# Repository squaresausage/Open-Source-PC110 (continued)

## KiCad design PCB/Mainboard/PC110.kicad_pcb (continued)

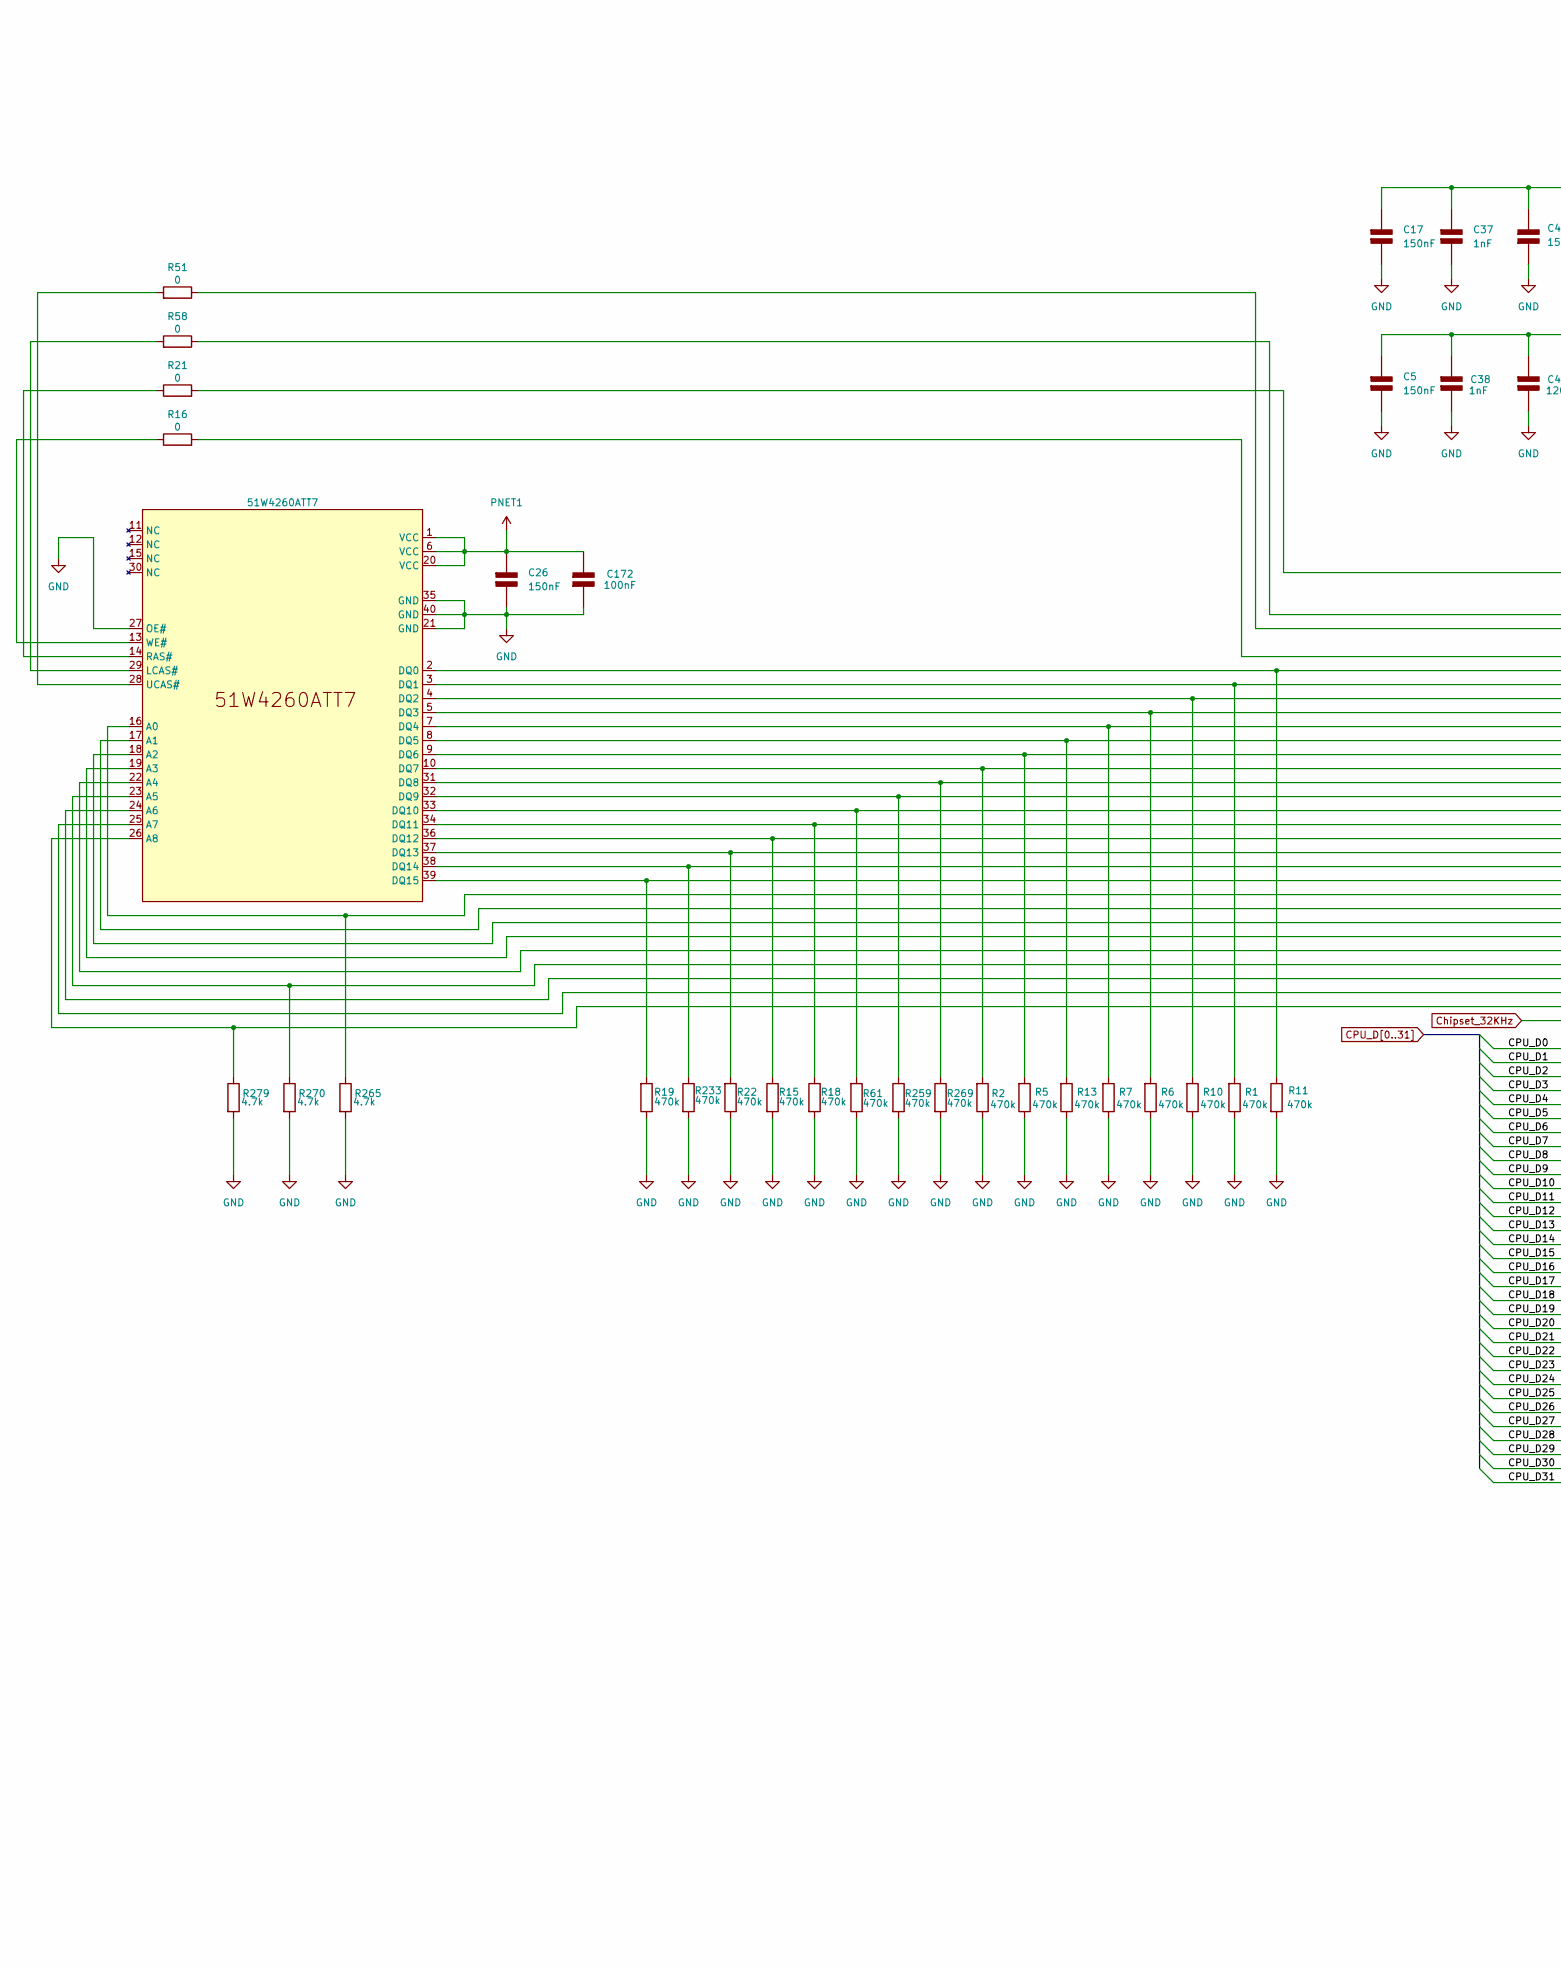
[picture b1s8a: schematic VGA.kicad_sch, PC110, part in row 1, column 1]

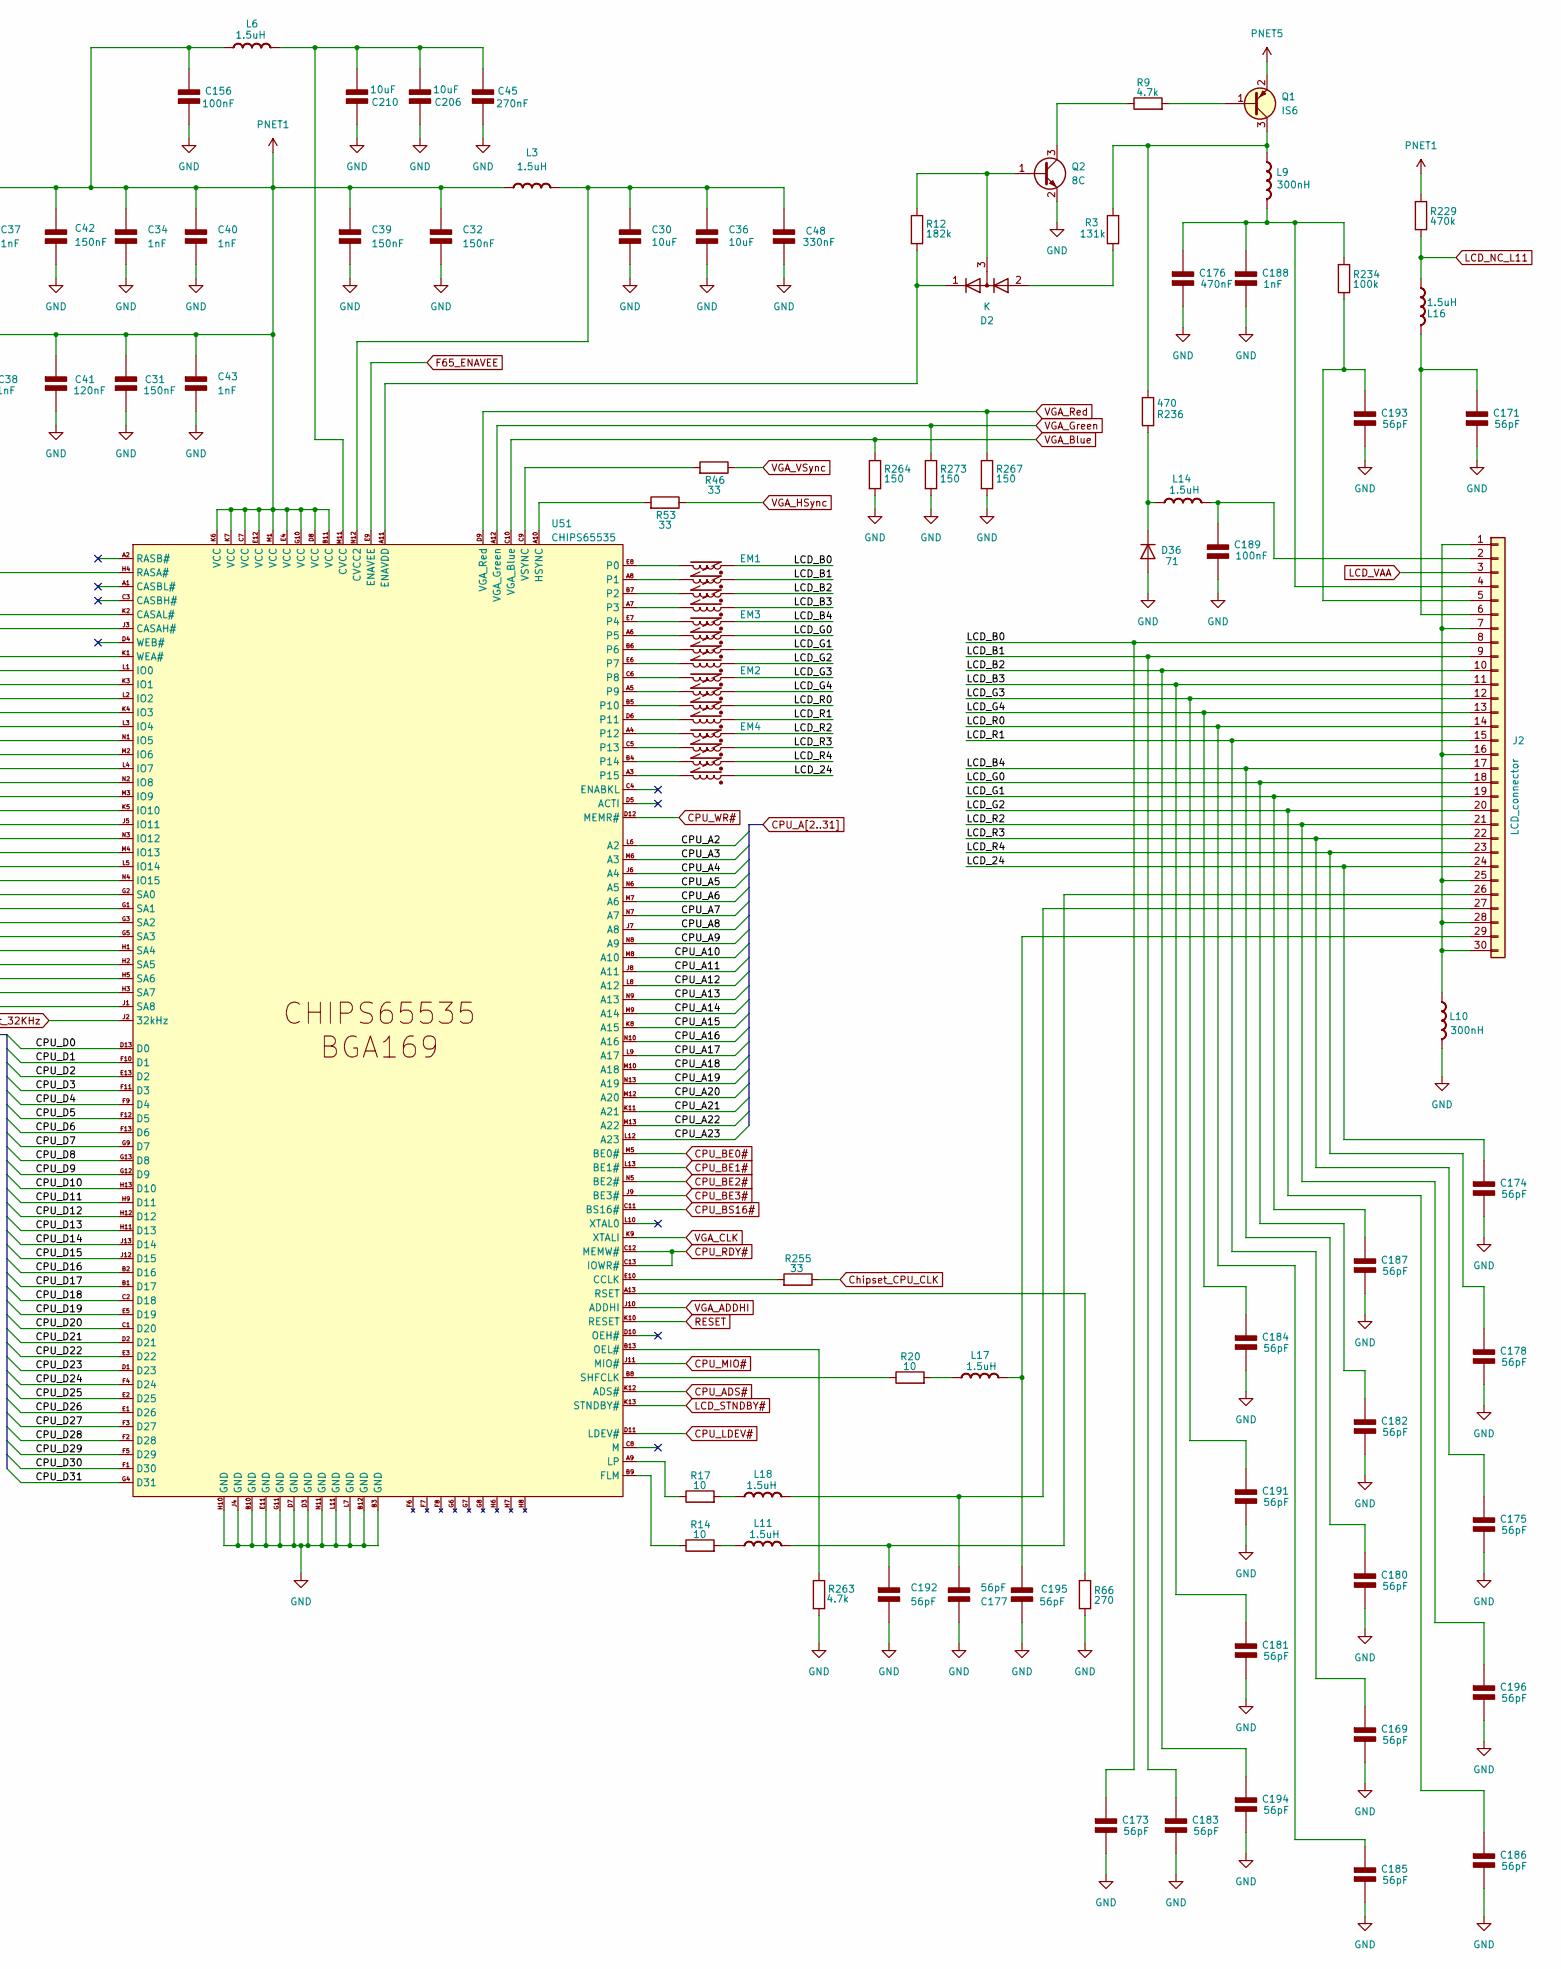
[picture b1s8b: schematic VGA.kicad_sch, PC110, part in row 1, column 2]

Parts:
C5, C17, C26, C31, C32, C39, C42: 150nF; C_0402_1005Metric
C30, C36, C206, C210: 10uF; C_1206_3216Metric
C34, C37, C38, C40, C43, C188: 1nF; C_0402_1005Metric
C41: 120nF; C_0402_1005Metric
C45: 270nF; C_0603_1608Metric
C48: 330nF; C_0402_1005Metric
C156, C172, C189: 100nF; C_0402_1005Metric
C169, C171, C173, C174, C175, C177, C178, C180, C181, C182, C183, C184, C185, C186, C187, C191, C192, C193, C194, C195, C196: 56pF; C_0402_1005Metric
C176: 470nF; C_0603_1608Metric
D2: K; SOT-416L
D36: 71; D_0603_1608Metric
EM1, EM2, EM3, EM4: R-array
J2: LCD_connector
L3, L6, L11, L14, L16, L17, L18: 1.5uH; L_0603_1608Metric
L9, L10: 300nH; L_0805_2012Metric
Q1: IS6; SOT-23
Q2: 8C; SOT-416
R1, R2, R5, R6, R7, R10, R11, R13, R15, R18, R19, R22, R61, R229, R233, R259, R269: 470k; R_0402_1005Metric
R3: 131k; R_0402_1005Metric
R9, R263, R265, R270, R279: 4.7k; R_0402_1005Metric
R12: 182k; R_0402_1005Metric
R14, R17, R20: 10; R_0402_1005Metric
R16, R21, R51, R58: 0; R_0402_1005Metric
R46, R53, R255: 33; R_0402_1005Metric
R66: 270; R_0402_1005Metric
R234: 100k; R_0402_1005Metric
R236: 470; R_0402_1005Metric
R264, R267, R273: 150; R_0805_2012Metric
U8: 51W4260ATT7; GRAMchip
U51: CHIPS65535; BGA-169

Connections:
/VGA Controller/LCD_24: C174.1 (+), EM4.1, J2.24
/VGA Controller/LCD_B0: C173.1 (+), EM1.4, J2.8
/VGA Controller/LCD_B1: C183.1 (+), EM1.3, J2.9
/VGA Controller/LCD_B2: C194.1 (+), EM1.2, J2.10
/VGA Controller/LCD_B3: C181.1 (+), EM1.1, J2.11
/VGA Controller/LCD_B4: C180.1 (+), EM3.4, J2.17
/VGA Controller/LCD_G0: C182.1 (+), EM3.3, J2.18
/VGA Controller/LCD_G1: C187.1 (+), EM3.2, J2.19
/VGA Controller/LCD_G2: C186.1 (+), EM3.1, J2.20
/VGA Controller/LCD_G3: C191.1 (+), EM2.4, J2.12
/VGA Controller/LCD_G4: C184.1 (+), EM2.3, J2.13
/VGA Controller/LCD_R0: C185.1 (+), EM2.2, J2.14
/VGA Controller/LCD_R1: C169.1 (+), EM2.1, J2.15
/VGA Controller/LCD_R2: C196.1 (+), EM4.4, J2.21
/VGA Controller/LCD_R3: C175.1 (+), EM4.3, J2.22
/VGA Controller/LCD_R4: C178.1 (+), EM4.2, J2.23
CPU_A2: U51.L6 (A2); also elsewhere on the board
CPU_A3: U51.M6 (A3); also elsewhere on the board
CPU_A4: U51.J6 (A4); also elsewhere on the board
CPU_A5: U51.N6 (A5); also elsewhere on the board
CPU_A6: U51.M7 (A6); also elsewhere on the board
CPU_A7: U51.N7 (A7); also elsewhere on the board
CPU_A8: U51.J7 (A8); also elsewhere on the board
CPU_A9: U51.N8 (A9); also elsewhere on the board
CPU_A10: U51.M8 (A10); also elsewhere on the board
CPU_A11: U51.J8 (A11); also elsewhere on the board
CPU_A12: U51.L8 (A12); also elsewhere on the board
CPU_A13: U51.N9 (A13); also elsewhere on the board
CPU_A14: U51.M9 (A14); also elsewhere on the board
CPU_A15: U51.K8 (A15); also elsewhere on the board
CPU_A16: U51.N10 (A16); also elsewhere on the board
CPU_A17: U51.L9 (A17); also elsewhere on the board
CPU_A18: U51.M10 (A18); also elsewhere on the board
CPU_A19: U51.N13 (A19); also elsewhere on the board
CPU_A20: U51.M12 (A20); also elsewhere on the board
CPU_A21: U51.K11 (A21); also elsewhere on the board
CPU_A22: U51.M13 (A22); also elsewhere on the board
CPU_A23: U51.L12 (A23); also elsewhere on the board
CPU_ADS#: U51.K12 (ADS#); also elsewhere on the board
CPU_BE0#: U51.M5 (BE0#); also elsewhere on the board
CPU_BE1#: U51.L13 (BE1#); also elsewhere on the board
CPU_BE2#: U51.N5 (BE2#); also elsewhere on the board
CPU_BE3#: U51.J9 (BE3#); also elsewhere on the board
CPU_BS16#: U51.C11 (BS16#); also elsewhere on the board
CPU_D0: U51.D13 (D0); also elsewhere on the board
CPU_D1: U51.F10 (D1); also elsewhere on the board
CPU_D2: U51.E13 (D2); also elsewhere on the board
CPU_D3: U51.F11 (D3); also elsewhere on the board
CPU_D4: U51.F9 (D4); also elsewhere on the board
CPU_D5: U51.F12 (D5); also elsewhere on the board
CPU_D6: U51.F13 (D6); also elsewhere on the board
CPU_D7: U51.G9 (D7); also elsewhere on the board
CPU_D8: U51.G13 (D8); also elsewhere on the board
CPU_D9: U51.G12 (D9); also elsewhere on the board
CPU_D10: U51.H13 (D10); also elsewhere on the board
CPU_D11: U51.H9 (D11); also elsewhere on the board
CPU_D12: U51.H12 (D12); also elsewhere on the board
CPU_D13: U51.H11 (D13); also elsewhere on the board
CPU_D14: U51.J13 (D14); also elsewhere on the board
CPU_D15: U51.J12 (D15); also elsewhere on the board
CPU_D16: U51.B2 (D16); also elsewhere on the board
CPU_D17: U51.B1 (D17); also elsewhere on the board
CPU_D18: U51.C2 (D18); also elsewhere on the board
CPU_D19: U51.E5 (D19); also elsewhere on the board
CPU_D20: U51.C1 (D20); also elsewhere on the board
CPU_D21: U51.D2 (D21); also elsewhere on the board
CPU_D22: U51.E3 (D22); also elsewhere on the board
CPU_D23: U51.D1 (D23); also elsewhere on the board
CPU_D24: U51.F4 (D24); also elsewhere on the board
CPU_D25: U51.E2 (D25); also elsewhere on the board
CPU_D26: U51.E1 (D26); also elsewhere on the board
CPU_D27: U51.F3 (D27); also elsewhere on the board
CPU_D28: U51.F2 (D28); also elsewhere on the board
CPU_D29: U51.F5 (D29); also elsewhere on the board
CPU_D30: U51.F1 (D30); also elsewhere on the board
CPU_D31: U51.G4 (D31); also elsewhere on the board
CPU_LDEV#: U51.D11 (LDEV#); also elsewhere on the board
CPU_MIO#: U51.J11 (MIO#); also elsewhere on the board
CPU_RDY#: U51.C12 (MEMW#), U51.C13 (IOWR#); also elsewhere on the board
CPU_WR#: U51.D12 (MEMR#); also elsewhere on the board
Chipset_32KHz: U51.J2 (32kHz); also elsewhere on the board
Chipset_CPU_CLK: R255.1; also elsewhere on the board
F65_ENAVEE: U51.E9 (ENAVEE); also elsewhere on the board
LCD_NC_L11: L16.2 (-), R229.1; also elsewhere on the board
LCD_STNDBY#: U51.K13 (STNDBY#); also elsewhere on the board
LCD_VAA: J2.3; also elsewhere on the board
unnamed: C30.2 (-), C36.2 (-), C48.1 (+), L3.2 (-), U51.N12 (CVCC2)
unnamed: C171.1 (+), J2.6, L16.1 (+)
unnamed: C176.1 (+), C188.1 (+), J2.4, L9.1 (+), R234.2
unnamed: C177.2 (-), J2.27, L18.1 (+)
unnamed: C189.2 (-), J2.2, L14.1 (+)
unnamed: C192.1 (+), J2.26, L11.2 (-)
unnamed: C193.1 (+), J2.5, R234.1
unnamed: C195.2 (-), J2.29, L17.2 (-)
unnamed: C45.1 (+), C206.2 (-), C210.2 (-), L6.1 (+), U51.M11 (CVCC)
unnamed: D2.2 (A), R3.1
unnamed: D2.1 (K), R12.2, U51.A11 (ENAVDD)
unnamed: D2.3 (common), Q2.1 (B), R12.1
unnamed: D36.1 (K), L14.2 (-), R236.2
unnamed: J2.1, J2.7, J2.16, J2.25, J2.28, J2.30, L10.1 (+)
unnamed: L9.2 (-), Q1.3 (C), R3.2, R236.1
unnamed: L11.1 (+), R14.2
unnamed: L17.1 (+), R20.2
unnamed: L18.2 (-), R17.2
unnamed: Q1.1 (B), R9.2
unnamed: Q2.3 (C), R9.1
unnamed: R58.2, U8.29 (LCAS#)
unnamed: R21.1, U8.14 (RAS#)
unnamed: R51.2, U8.28 (UCAS#)
unnamed: R16.1, U8.13 (WE#)
unnamed: R51.1, U51.J3 (CASAH#)
unnamed: R58.1, U51.K2 (CASAL#)
unnamed: R255.2, U51.E10 (CCLK)
unnamed: R14.1, U51.B9 (FLM)
unnamed: R53.2, U51.A10 (HSYNC)
unnamed: R11.1, U8.2 (DQ0), U51.L1 (IO0)
unnamed: R1.2, U8.3 (DQ1), U51.K3 (IO1)
unnamed: R10.2, U8.4 (DQ2), U51.L2 (IO2)
unnamed: R6.2, U8.5 (DQ3), U51.K4 (IO3)
unnamed: R7.2, U8.7 (DQ4), U51.L3 (IO4)
unnamed: R13.2, U8.8 (DQ5), U51.N1 (IO5)
unnamed: R5.2, U8.9 (DQ6), U51.M2 (IO6)
unnamed: R2.2, U8.10 (DQ7), U51.L4 (IO7)
unnamed: R269.1, U8.31 (DQ8), U51.N2 (IO8)
unnamed: R259.1, U8.32 (DQ9), U51.M3 (IO9)
unnamed: R61.2, U8.33 (DQ10), U51.K5 (IO10)
unnamed: R18.1, U8.34 (DQ11), U51.J5 (IO11)
unnamed: R15.1, U8.36 (DQ12), U51.N3 (IO12)
unnamed: R22.2, U8.37 (DQ13), U51.M4 (IO13)
unnamed: R233.1, U8.38 (DQ14), U51.L5 (IO14)
unnamed: R19.2, U8.39 (DQ15), U51.N4 (IO15)
unnamed: R17.1, U51.A9 (LP)
unnamed: R263.1, U51.B13 (OEL#)
unnamed: EM1.5, U51.E8 (P0)
unnamed: EM1.6, U51.A8 (P1)
unnamed: EM1.7, U51.B7 (P2)
unnamed: EM1.8, U51.A7 (P3)
unnamed: EM3.5, U51.E7 (P4)
unnamed: EM3.6, U51.A6 (P5)
unnamed: EM3.7, U51.B6 (P6)
unnamed: EM3.8, U51.E6 (P7)
unnamed: EM2.5, U51.C6 (P8)
unnamed: EM2.6, U51.A5 (P9)
unnamed: EM2.7, U51.B5 (P10)
unnamed: EM2.8, U51.D6 (P11)
unnamed: EM4.5, U51.A4 (P12)
unnamed: EM4.6, U51.C5 (P13)
unnamed: EM4.7, U51.B4 (P14)
unnamed: EM4.8, U51.A3 (P15)
unnamed: R21.2, U51.H4 (RASA#)
unnamed: R66.2, U51.A13 (RSET)
unnamed: R265.1, U8.16 (A0), U51.G2 (SA0)
unnamed: U8.17 (A1), U51.G1 (SA1)
unnamed: U8.18 (A2), U51.G3 (SA2)
unnamed: U8.19 (A3), U51.G5 (SA3)
unnamed: U8.22 (A4), U51.H1 (SA4)
unnamed: R270.1, U8.23 (A5), U51.H2 (SA5)
unnamed: U8.24 (A6), U51.H5 (SA6)
unnamed: U8.25 (A7), U51.H3 (SA7)
unnamed: R279.1, U8.26 (A8), U51.J1 (SA8)
unnamed: R20.1, U51.B8 (SHFCLK)
unnamed: R46.2, U51.C9 (VSYNC)
unnamed: R16.2, U51.K1 (WEA#)
PNET1: C5.1 (+), C17.1 (+), C26.1 (+), C31.2 (-), C32.1 (+), C34.1 (+), C37.1 (+), C38.1 (+), C39.1 (+), C40.1 (+), C41.1 (+), C42.2 (-), C43.1 (+), C156.2 (-), C172.2 (-), L3.1 (+), L6.2 (-), R229.2, U8.1 (VCC), U8.6 (VCC), U8.20 (VCC), U51.B11 (VCC), U51.C7 (VCC), U51.D8 (VCC), U51.E4 (VCC), U51.E12 (VCC), U51.G10 (VCC), U51.K6 (VCC), U51.K7 (VCC), U51.M1 (VCC); also elsewhere on the board
RESET: U51.K10 (RESET); also elsewhere on the board
VGA_ADDHI: U51.J10 (ADDHI); also elsewhere on the board
VGA_Blue: R264.1, U51.C10 (VGA_Blue); also elsewhere on the board
VGA_CLK: U51.K9 (XTALI); also elsewhere on the board
VGA_Green: R273.1, U51.A12 (VGA_Green); also elsewhere on the board
VGA_HSync: R53.1; also elsewhere on the board
VGA_Red: R267.1, U51.D9 (VGA_Red); also elsewhere on the board
VGA_VSync: R46.1; also elsewhere on the board

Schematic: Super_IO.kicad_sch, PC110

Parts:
C83, C84, C120: 100nF; C_0402_1005Metric
C244: 120nF; C_0402_1005Metric
C247: 1nF; C_0402_1005Metric
D24, D25: 3D
R118, R310: 100k; R_0402_1005Metric
R132, R133, R137: 2k; R_0402_1005Metric
R136, R138, R140, R141, R142, R319: 1k; R_0402_1005Metric
R143: 10k; R_0402_1005Metric
R314, R315: 470k; R_0402_1005Metric
U22: FDC37C665IR; FDC
U23: EA; SOT-353
U25: E4; SOT-353

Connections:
AEN: U22.44 (AEN); also elsewhere on the board
Chipset_FDC_TC: U22.33 (TC); also elsewhere on the board
FCS_IOCHRDY: U22.98 (IOCHRDY); also elsewhere on the board
FDC_ACK#: R136.1, U22.60 (ACK#); also elsewhere on the board
FDC_AUTOFD#: R141.1, U22.74 (AUTOFD#); also elsewhere on the board
FDC_BUSY: R143.2, U22.59 (BUSY); also elsewhere on the board
FDC_CLK: U22.18 (X1/CLK1); also elsewhere on the board
FDC_CTS1#: U22.80 (CTS1#); also elsewhere on the board
FDC_CTS2#: U22.90 (CTS2#); also elsewhere on the board
FDC_DACK#: R118.1, U22.34 (DACK#); also elsewhere on the board
FDC_DCD1#: U22.83 (DCD1#); also elsewhere on the board
FDC_DCD2#: U22.85 (DCD2#); also elsewhere on the board
FDC_DIR#: U22.5 (DIR#); also elsewhere on the board
FDC_DRATE0: U22.17 (DRATE0); also elsewhere on the board
FDC_DRATE1: U22.16 (DRATE1); also elsewhere on the board
FDC_DS3: U22.95 (A10); also elsewhere on the board
FDC_DSKCHG#: U22.15 (DSKCHG#); also elsewhere on the board
FDC_DSR1: U22.78 (DSR1); also elsewhere on the board
FDC_DSR2#: U22.88 (DSR2#); also elsewhere on the board
FDC_DTR1#: U22.81 (DTR1#); also elsewhere on the board
FDC_DTR2#: U22.91 (DTR2#); also elsewhere on the board
FDC_ERROR#: R142.1, U22.73 (ERROR#); also elsewhere on the board
FDC_FDRQ: U22.50 (FDRQ); also elsewhere on the board
FDC_FINTR: U22.38 (FINTR); also elsewhere on the board
FDC_HDCS0#: U22.23 (HDCS0#); also elsewhere on the board
FDC_HDCS1#: U22.24 (HDCS1#); also elsewhere on the board
FDC_HDSEL#: U22.9 (HDSEL#); also elsewhere on the board
FDC_IDE7: U22.20 (IDED7); also elsewhere on the board
FDC_INIT#: R133.1, U22.72 (INIT#); also elsewhere on the board
FDC_IOW: U23.2; also elsewhere on the board
FDC_IRRX_RXD2: R315.1, U22.86 (IRRX/RXD2); also elsewhere on the board
FDC_IRTX_TXD2: U22.87 (IRTX/TXD2); also elsewhere on the board
FDC_MTR2#: R310.1, U22.94 (MTR2#); also elsewhere on the board
FDC_MTR3#: U22.97 (MTR3#); also elsewhere on the board
FDC_PD0: U22.69 (PD0); also elsewhere on the board
FDC_PD1: U22.68 (PD1); also elsewhere on the board
FDC_PD2: U22.67 (PD2); also elsewhere on the board
FDC_PD3: U22.66 (PD3); also elsewhere on the board
FDC_PD4: U22.64 (PD4); also elsewhere on the board
FDC_PD5: U22.63 (PD5); also elsewhere on the board
FDC_PD6: U22.62 (PD6); also elsewhere on the board
FDC_PD7: U22.61 (PD7); also elsewhere on the board
FDC_PE: R138.1, U22.58 (PE); also elsewhere on the board
FDC_RDATA#: U22.14 (RDATA#); also elsewhere on the board
FDC_RI1#: U22.82 (RI1#); also elsewhere on the board
FDC_RI2#: U22.84 (RI2#); also elsewhere on the board
FDC_RTS1#: U22.79 (RTS1#); also elsewhere on the board
FDC_RTS2#: U22.89 (RTS2#); also elsewhere on the board
FDC_RXD1: U22.76 (RXD1); also elsewhere on the board
FDC_SLCT: R140.2, U22.57 (SLCT); also elsewhere on the board
FDC_SLCTIN#: R132.1, U22.71 (SLCTIN#); also elsewhere on the board
FDC_STEP#: U22.6 (STEP#); also elsewhere on the board
FDC_STROBE#: R137.1, U22.75 (STROBE#); also elsewhere on the board
FDC_TRK0#: U22.11 (TRK0#); also elsewhere on the board
FDC_TXD1: U22.77 (TXD1); also elsewhere on the board
FDC_WDATA#: U22.7 (WDATA#); also elsewhere on the board
FDC_WGATE#: U22.8 (WGATE#); also elsewhere on the board
FDC_WRTPRT#: U22.12 (WRTPRT#); also elsewhere on the board
FDD_DRSEL: U22.2 (DS0#); also elsewhere on the board
FDD_INDEX#: U22.10 (INDEX#); also elsewhere on the board
FDD_MOTEN: U22.100 (MTR0#); also elsewhere on the board
IOCS16#: R319.2, U22.25 (IOCS16#); also elsewhere on the board
IOR#: U22.42 (IOR#); also elsewhere on the board
IOW#: U25.2; also elsewhere on the board
IRQ3: U22.35 (IRQ3); also elsewhere on the board
IRQ4: U22.36 (IRQ4); also elsewhere on the board
IRQ5: U22.92 (DRV2/ADRx/PINTR2); also elsewhere on the board
IRQ7: U22.37 (PINTR); also elsewhere on the board
unnamed: D24.2 (K), R132.2, R136.2, R137.2, R141.2
unnamed: D25.2 (K), R133.2, R138.2, R140.1, R142.2, R143.1
unnamed: U22.43 (IOW#), U25.4
unnamed: U23.4, U25.1
PNET1: C83.1 (+), C247.1, R118.2, R310.2, U22.13 (VCC), U22.70 (VCC), U23.5 (VCC), U25.5 (VCC); also elsewhere on the board
PNET7: R319.1; also elsewhere on the board
PWRGD: R314.1, U22.56 (PWRGD); also elsewhere on the board
RESET: U22.55 (RESET); also elsewhere on the board
SA0: U22.26 (A0); also elsewhere on the board
SA1: U22.27 (A1); also elsewhere on the board
SA2: U22.28 (A2); also elsewhere on the board
SA3: U22.29 (A3); also elsewhere on the board
SA4: U22.30 (A4); also elsewhere on the board
SA5: U22.31 (A5); also elsewhere on the board
SA6: U22.32 (A6); also elsewhere on the board
SA7: U22.39 (A7); also elsewhere on the board
SA8: U22.40 (A8); also elsewhere on the board
SA9: U22.41 (A9); also elsewhere on the board
SD0: U22.46 (D0); also elsewhere on the board
SD1: U22.47 (D1); also elsewhere on the board
SD2: U22.48 (D2); also elsewhere on the board
SD3: U22.49 (D3); also elsewhere on the board
SD4: U22.51 (D4); also elsewhere on the board
SD5: U22.52 (D5); also elsewhere on the board
SD6: U22.53 (D6); also elsewhere on the board
SD7: U22.54 (D7); also elsewhere on the board

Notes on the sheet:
Device_Address_BUS
Device_Data_BUS

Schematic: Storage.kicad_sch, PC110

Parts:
C94, C129, C133, C141, C146, C236, C241, C263: 100nF; C_0402_1005Metric
C131: 10nF; C_0603_1608Metric
C132: 100nF; C_0603_1608Metric
C134: 150nF; C_0603_1608Metric
C142, C143, C271, C272: 150nF; C_0402_1005Metric
C144, C145: 100pF; C_0402_1005Metric
C262: 1.5uF; C_0805_2012Metric
C266: 180pF; C_0402_1005Metric
C269: 220pF; C_0402_1005Metric
F4: 0.5A; Fuse_1206_3216Metric
J11: CF-card
Q37: BH RT; SOT-89-3
R131, R184: DNP; R_0402_1005Metric; not fitted
R134, R365: 10k; R_0402_1005Metric
R145, R290, R296, R298, R301: DNP; R_0402_1005Metric
R161, R173, R360, R361: 470k; R_0402_1005Metric
R292: DNP; R_0805_2012Metric
R295, R299, R366, R367: 0; R_0402_1005Metric
R300: 0; R_0805_2012Metric
R362, R371: 2k; R_0402_1005Metric
R368: 1.5k; R_0402_1005Metric
R369: 22k; R_0402_1005Metric
R373, R374, R375, R376, R377, R378, R380, R381: 4.7k; R_0402_1005Metric
U27: AT29LV512-12TU; Flash-32
U41: SDLB-4; SanDisk
U42: SC414281PU4; QFN-100
U56: SN74LV32; TSSOP-14_4.4x5mm_P0.65mm
U65: E4; SOT-353
U68: SN74LV08; TSSOP-14_4.4x5mm_P0.65mm

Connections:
CF_CD1_Pluto: J11.2 (CD1#), R173.2; also elsewhere on the board
CF_CD2_Pluto: J11.49 (CD2#), R161.1; also elsewhere on the board
FCS_BVD1: J11.42 (BVD1), U42.50 (BVD1)
FCS_BVD2: J11.40 (BVD2), U42.49 (BVD2)
FCS_IOCHRDY: J11.34 (IOCHRDY), U42.47 (WAIT); also elsewhere on the board
FCS_RESET: J11.32 (RESET), R184.1, U42.36 (RESET); also elsewhere on the board
FDC_HDCS0#: R366.2, U68.1; also elsewhere on the board
FDC_HDCS1#: R367.2, U68.2; also elsewhere on the board
FDC_IDE7: J11.11 (SD7), R369.2, U42.13 (HD7); also elsewhere on the board
IOCS16#: J11.47 (IOCS16#), U42.52 (IO16); also elsewhere on the board
IOR#: R295.2, R296.1, U56.1; also elsewhere on the board
IOW#: R298.2, R299.2, U56.4; also elsewhere on the board
IRQ14: J11.24 (IRQ14), R365.1, U42.46 (RDY); also elsewhere on the board
unnamed: C129.1 (+), C272.1 (+), F4.2, J11.25 (VCC), J11.26 (VCC)
unnamed: C266.1, C269.2
unnamed: C266.2, R362.2
unnamed: J11.13 (CE1#), R361.1, R366.1, U42.37 (CE1)
unnamed: J11.14 (CE2#), R360.1, R367.1, U42.39 (CE2)
unnamed: J11.28 (CSEL#), R145.2
unnamed: J11.18 (IOR#), R295.1, R301.2
unnamed: J11.20 (IOW#), R290.2, R299.1
unnamed: Q37.1 (B), R368.1
unnamed: R368.2, U65.4
unnamed: U27.20 (MA0), U42.74 (MA0)
unnamed: U27.19 (MA1), U42.75 (MA1)
unnamed: U27.18 (MA2), U42.76 (MA2)
unnamed: U27.17 (MA3), U42.77 (MA3)
unnamed: U27.16 (MA4), U42.78 (MA4)
unnamed: U27.15 (MA5), U42.79 (MA5)
unnamed: U27.14 (MA6), U42.80 (MA6)
unnamed: U27.13 (MA7), U42.81 (MA7)
unnamed: U27.3 (MA8), U42.83 (MA8)
unnamed: U27.2 (MA9), U42.84 (MA9)
unnamed: U27.31 (MA10), U42.85 (MA10)
unnamed: U27.1 (MA11), U42.86 (MA11)
unnamed: U27.12 (MA12), U42.87 (MA12)
unnamed: U27.4 (MA13), U42.89 (MA13)
unnamed: U27.5 (MA14), U42.90 (MA14)
unnamed: U27.11 (MA15), U42.91 (MA15)
unnamed: U27.21 (MD0), U42.92 (MD0)
unnamed: U27.22 (MD1), U42.93 (MD1)
unnamed: U27.23 (MD2), U42.95 (MD2)
unnamed: U27.25 (MD3), U42.96 (MD3)
unnamed: U27.26 (MD4), U42.97 (MD4)
unnamed: U27.27 (MD5), U42.98 (MD5)
unnamed: U27.28 (MD6), U42.99 (MD6)
unnamed: U27.29 (MD7), U42.100 (MD7)
unnamed: U27.30 (ROMCEL0#), U42.71 (ROMCEL0)
unnamed: U27.32 (ROMOEL#), U42.72 (ROMOEL)
unnamed: R131.2, R134.1, U27.7 (ROMWEL#), U42.73 (ROMWEL)
unnamed: U41.7 (CS), U42.55 (CS)
unnamed: C141.1, U41.20 (Cext2)
unnamed: C143.1, U41.21 (Cext3)
unnamed: C142.1, C144.2, U41.22 (Cext4)
unnamed: C141.2, C145.2, U41.23 (Cext5)
unnamed: C146.1, U41.24 (Cext6)
unnamed: C142.2, U41.25 (Cext7)
unnamed: C143.2, U41.26 (Cext8)
unnamed: C146.2, U41.27 (Cext9)
unnamed: U41.4 (PD), U42.57 (PD)
unnamed: U41.5 (SCLK1), U42.53 (SCLK1)
unnamed: U41.1 (SI0), U42.59 (SI0)
unnamed: U41.2 (SI1), U42.58 (SI1)
unnamed: U41.13 (SO0), U42.62 (SO0)
unnamed: U41.17 (SO1), U42.60 (SO1)
unnamed: R362.1, R371.2, U42.12 (C_EXT)
unnamed: U42.66 (IO0), U65.1
unnamed: R296.2, R301.1, U42.42 (IORD), U56.3
unnamed: R290.1, R298.1, U42.43 (IOWR), U56.6
unnamed: R371.1, U42.11 (RC_IN)
unnamed: U56.2, U56.5, U68.3
PNET1: R161.2, R173.1, R292.1; also elsewhere on the board
PNET7: R300.1, R365.2, R373.2, R374.2, R375.2, R376.2, R377.2, R378.2, R380.2, R381.2; also elsewhere on the board
PNET12: C94.1, C133.1, C236.1, C241.2, C262.2, C263.2, C271.1, F4.1, Q37.3 (E), R134.2, R292.2, R300.2, R360.2, R361.2, R369.1, U27.8 (VCC), U42.5 (VCC), U42.15 (VCC), U42.38 (VCC), U42.56 (VCC), U42.65 (VCC), U42.88 (VCC), U56.14 (VCC), U65.5 (VCC), U68.14 (VCC)
SA0: J11.39 (SA0), U42.35 (SA0); also elsewhere on the board
SA1: J11.37 (SA1), U42.34 (SA1); also elsewhere on the board
SA2: J11.35 (SA2), U42.33 (SA2); also elsewhere on the board
SD0: J11.41 (SD0), R375.1, U42.22 (HD0); also elsewhere on the board
SD1: J11.43 (SD1), R374.1, U42.21 (HD1); also elsewhere on the board
SD2: J11.45 (SD2), R376.1, U42.19 (HD2); also elsewhere on the board
SD3: J11.3 (SD3), R373.1, U42.18 (HD3); also elsewhere on the board
SD4: J11.5 (SD4), R378.1, U42.17 (HD4); also elsewhere on the board
SD5: J11.7 (SD5), R377.1, U42.16 (HD5); also elsewhere on the board
SD6: J11.9 (SD6), R381.1, U42.14 (HD6); also elsewhere on the board
SD7: R380.1; also elsewhere on the board
SD8: J11.44 (SD8), U42.9 (HD8); also elsewhere on the board
SD9: J11.46 (SD9), U42.8 (HD9); also elsewhere on the board
SD10: J11.48 (SD10), U42.7 (HD10); also elsewhere on the board
SD11: J11.4 (SD11), U42.6 (HD11); also elsewhere on the board
SD12: J11.6 (SD12), U42.4 (HD12); also elsewhere on the board
SD13: J11.8 (SD13), U42.3 (HD13); also elsewhere on the board
SD14: J11.10 (SD14), U42.2 (HD14); also elsewhere on the board
SD15: J11.12 (SD15), U42.1 (HD15); also elsewhere on the board

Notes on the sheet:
Device_Data_BUS
Device_Address_BUS
